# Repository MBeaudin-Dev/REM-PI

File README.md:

# REM-PI

Firmware for the Raspberry Pis used by Robot Event Manager. A Pi runs in one
of two roles, assigned by an admin when it is paired:

- **Kiosk**: shows a display page in full-screen Chromium.
- **Field node**: shows the field display *and* drives the relay HAT that
  enables, disables and switches the mode of the robots on its field.

This README covers how the relay HAT works. The code is in
[`pi_firmware/hardware.py`](pi_firmware/hardware.py).

## The relay HAT

The HAT has two relays, each driven by one GPIO pin on the Pi. Together they
reproduce the two control lines of the VEX V5 legacy Competition Port:

| Relay  | Physical pin | BCM GPIO | Controls                        |
| ------ | ------------ | -------- | ------------------------------- |
| Enable | 11           | GPIO17   | Robots enabled or disabled      |
| Mode   | 29           | GPIO5    | Autonomous or driver (user) control |

The code uses `GPIO.BOARD` numbering, so the pins are referred to by their
physical header position (11 and 29), not their BCM numbers.

Setting a pin HIGH energizes its relay; setting it LOW de-energizes it.

## Robot states

The firmware only ever puts the HAT into one of three states:

| State          | Enable pin (11)     | Mode pin (29)       | Method                |
| -------------- | ------------------- | ------------------- | --------------------- |
| **Disabled**   | LOW (de-energized)  | LOW (de-energized)  | `disable()`           |
| **Autonomous** | HIGH (energized)    | LOW (de-energized)  | `enable_autonomous()` |
| **Driver**     | HIGH (energized)    | HIGH (energized)    | `enable_driver()`     |

With both relays de-energized the robots are disabled, so a crash, power loss
or unconfigured GPIO leaves the field in a safe state.

### Enable vs. disable

The **enable relay** decides whether robots may move at all.

- Enable pin **HIGH**: robots are **enabled**, in whichever mode the mode
  relay selects.
- Enable pin **LOW**: robots are **disabled**.

### Autonomous vs. driver

The **mode relay** decides which program the robots run while enabled.

- Mode pin **HIGH**: **driver (user) control**.
- Mode pin **LOW**: **autonomous**.

The mode pin only matters while the enable pin is HIGH. In the disabled state
the mode pin is left LOW.

## What triggers each state

The field node receives commands from the server over a WebSocket
([`pi_firmware/ws_client.py`](pi_firmware/ws_client.py)):

| Event                                        | Result     |
| -------------------------------------------- | ---------- |
| `phase_change` with `phase: "autonomous"`    | Autonomous |
| `phase_change` with `phase: "driver"`        | Driver     |
| `phase_change` with any other phase          | Disabled   |
| `estop`                                      | Disabled   |

The Pi also disables the robots on its own, without a command from the
server:

- **On startup**, as soon as the relay pins are set up.
- **If the server goes quiet** for 20 seconds (4 missed heartbeats), even if
  the connection still looks open.
- **If the connection to the server drops**, before each reconnect attempt.
- **On shutdown**, before releasing the GPIO pins.

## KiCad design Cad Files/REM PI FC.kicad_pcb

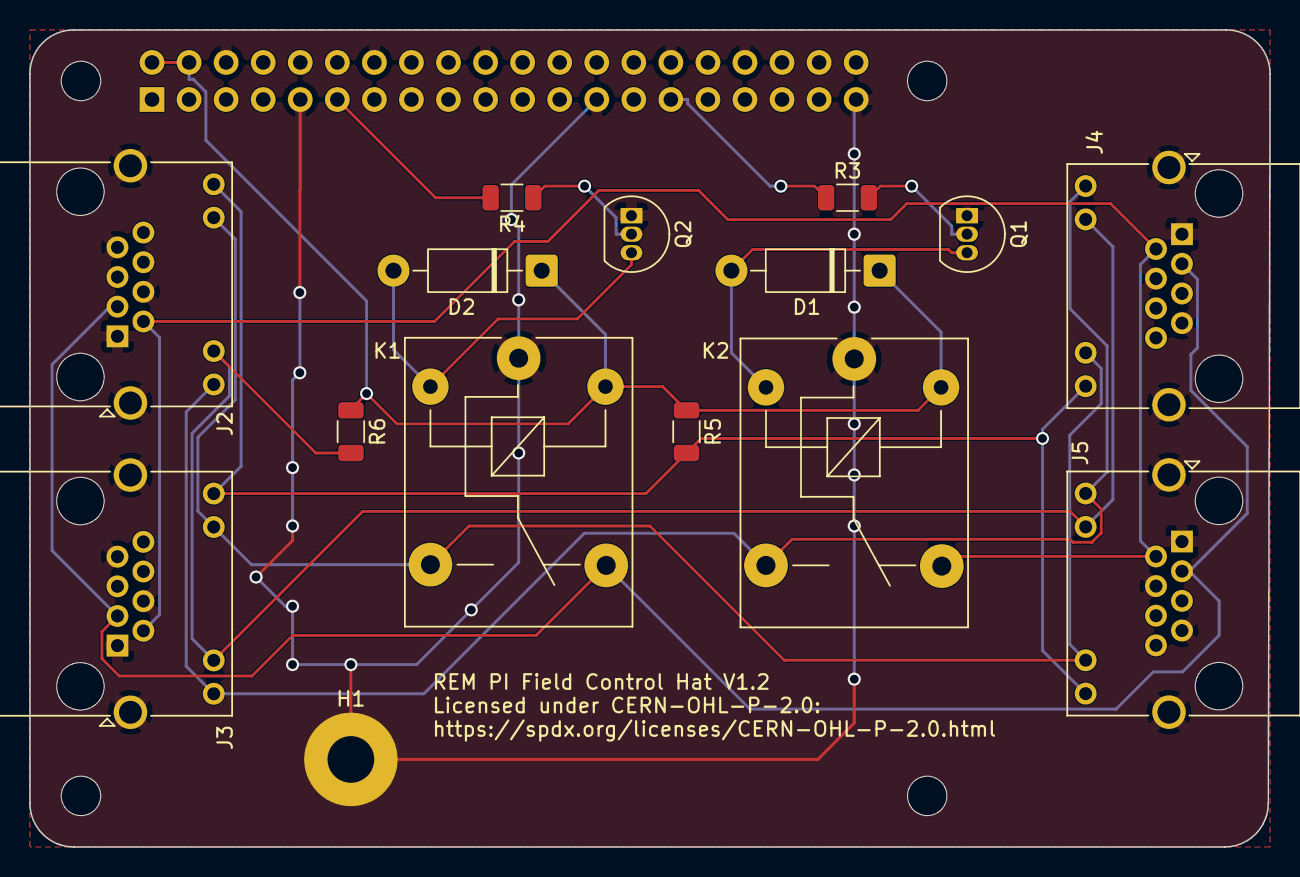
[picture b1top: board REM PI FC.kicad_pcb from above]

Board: 2 copper layers, 85.0 x 56.0 mm, 20 parts (1 on the bottom side), 15 nets.

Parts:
D1, D2: 1N4007; D_DO-41_SOD81_P10.16mm_Horizontal
H1: MountingHole_Pad; MountingHole_3.2mm_M3_Pad
J1: GPIO; PinSocket_2x20_P2.54mm_Vertical
J2, J3, J4, J5: RJ45_LED_Shielded; RJ45_Amphenol_RJHSE538X
K1-AD1, K2-Enable1: Songle SRD-5VDC-SL-C; Relay_SPDT_SANYOU_SRD_Series_Form_C
MH1, MH2, MH3, MH4: MountingHole_2.7mm_M2.5
Q1, Q2: PN2222A; TO-92_Inline
R3, R4: R1k; R_1206_3216Metric
R5, R6: R30; R_1206_3216Metric

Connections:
+3V3: J1.1, J1.17
+5V: D1.1 (K), D2.1 (K), J1.2, J1.4, K1-AD1.5, K2-Enable1.5, R5.1, R6.1
/GPIO5: J1.29, R3.1
/GPIO17: J1.11, R4.2
GND: H1.1 (1_1), J1.6, J1.9, J1.14, J1.20, J1.25, J1.30, J1.34, J1.39, J2.1, J2.4, J2.7, J2.SH, J3.1, J3.4, J3.7, J3.SH, J4.1, J4.4, J4.7, J4.SH, J5.1, J5.4, J5.7, J5.SH, K1-AD1.1, K2-Enable1.1, Q1.1 (E), Q2.1 (E)
unnamed: D1.2 (A), K1-AD1.2, Q1.3 (C)
unnamed: D2.2 (A), K2-Enable1.2, Q2.3 (C)
unnamed: J2.2, J3.2, J4.2, J5.2, K1-AD1.4
unnamed: J2.3, J3.3, J4.3, J5.3, K2-Enable1.4
unnamed: J2.9, J3.9, J4.9, J5.9, K1-AD1.3
unnamed: J2.10, J3.10, J4.10, J5.10, R6.2
unnamed: J2.11, J3.11, J4.11, J5.11, K2-Enable1.3
unnamed: J2.12, J3.12, J4.12, J5.12, R5.2
unnamed: Q1.2 (B), R3.2
unnamed: Q2.2 (B), R4.1

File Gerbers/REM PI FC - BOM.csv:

Comment,Designator,Footprint
1N4007,"D1,D2",Diode_THT:D_DO-41_SOD81_P10.16mm_Horizontal
KH-RJ45-56-8P8C-D,"J2,J3,J4,J5",Connector_RJ:RJ45_Amphenol_RJHSE538X
srd-05vdc-sl-c,"K1-AD1,K2-Enable1",Relay_THT:Relay_SPDT_SANYOU_SRD_Series_Form_C
PN2222A,"Q1,Q2",Package_TO_SOT_THT:TO-92
1206W4J0102T5E,"R3,R4",Resistor_SMD:R_1206_3216Metric
1206W4F300JT5E,"R5,R6",Resistor_SMD:R_1206_3216Metric

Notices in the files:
Cad Files/REM PI FC.kicad_pcb:
Licensed under CERN-OHL-P-2.0:
https://spdx.org/licenses/CERN-OHL-P-2.0.html
